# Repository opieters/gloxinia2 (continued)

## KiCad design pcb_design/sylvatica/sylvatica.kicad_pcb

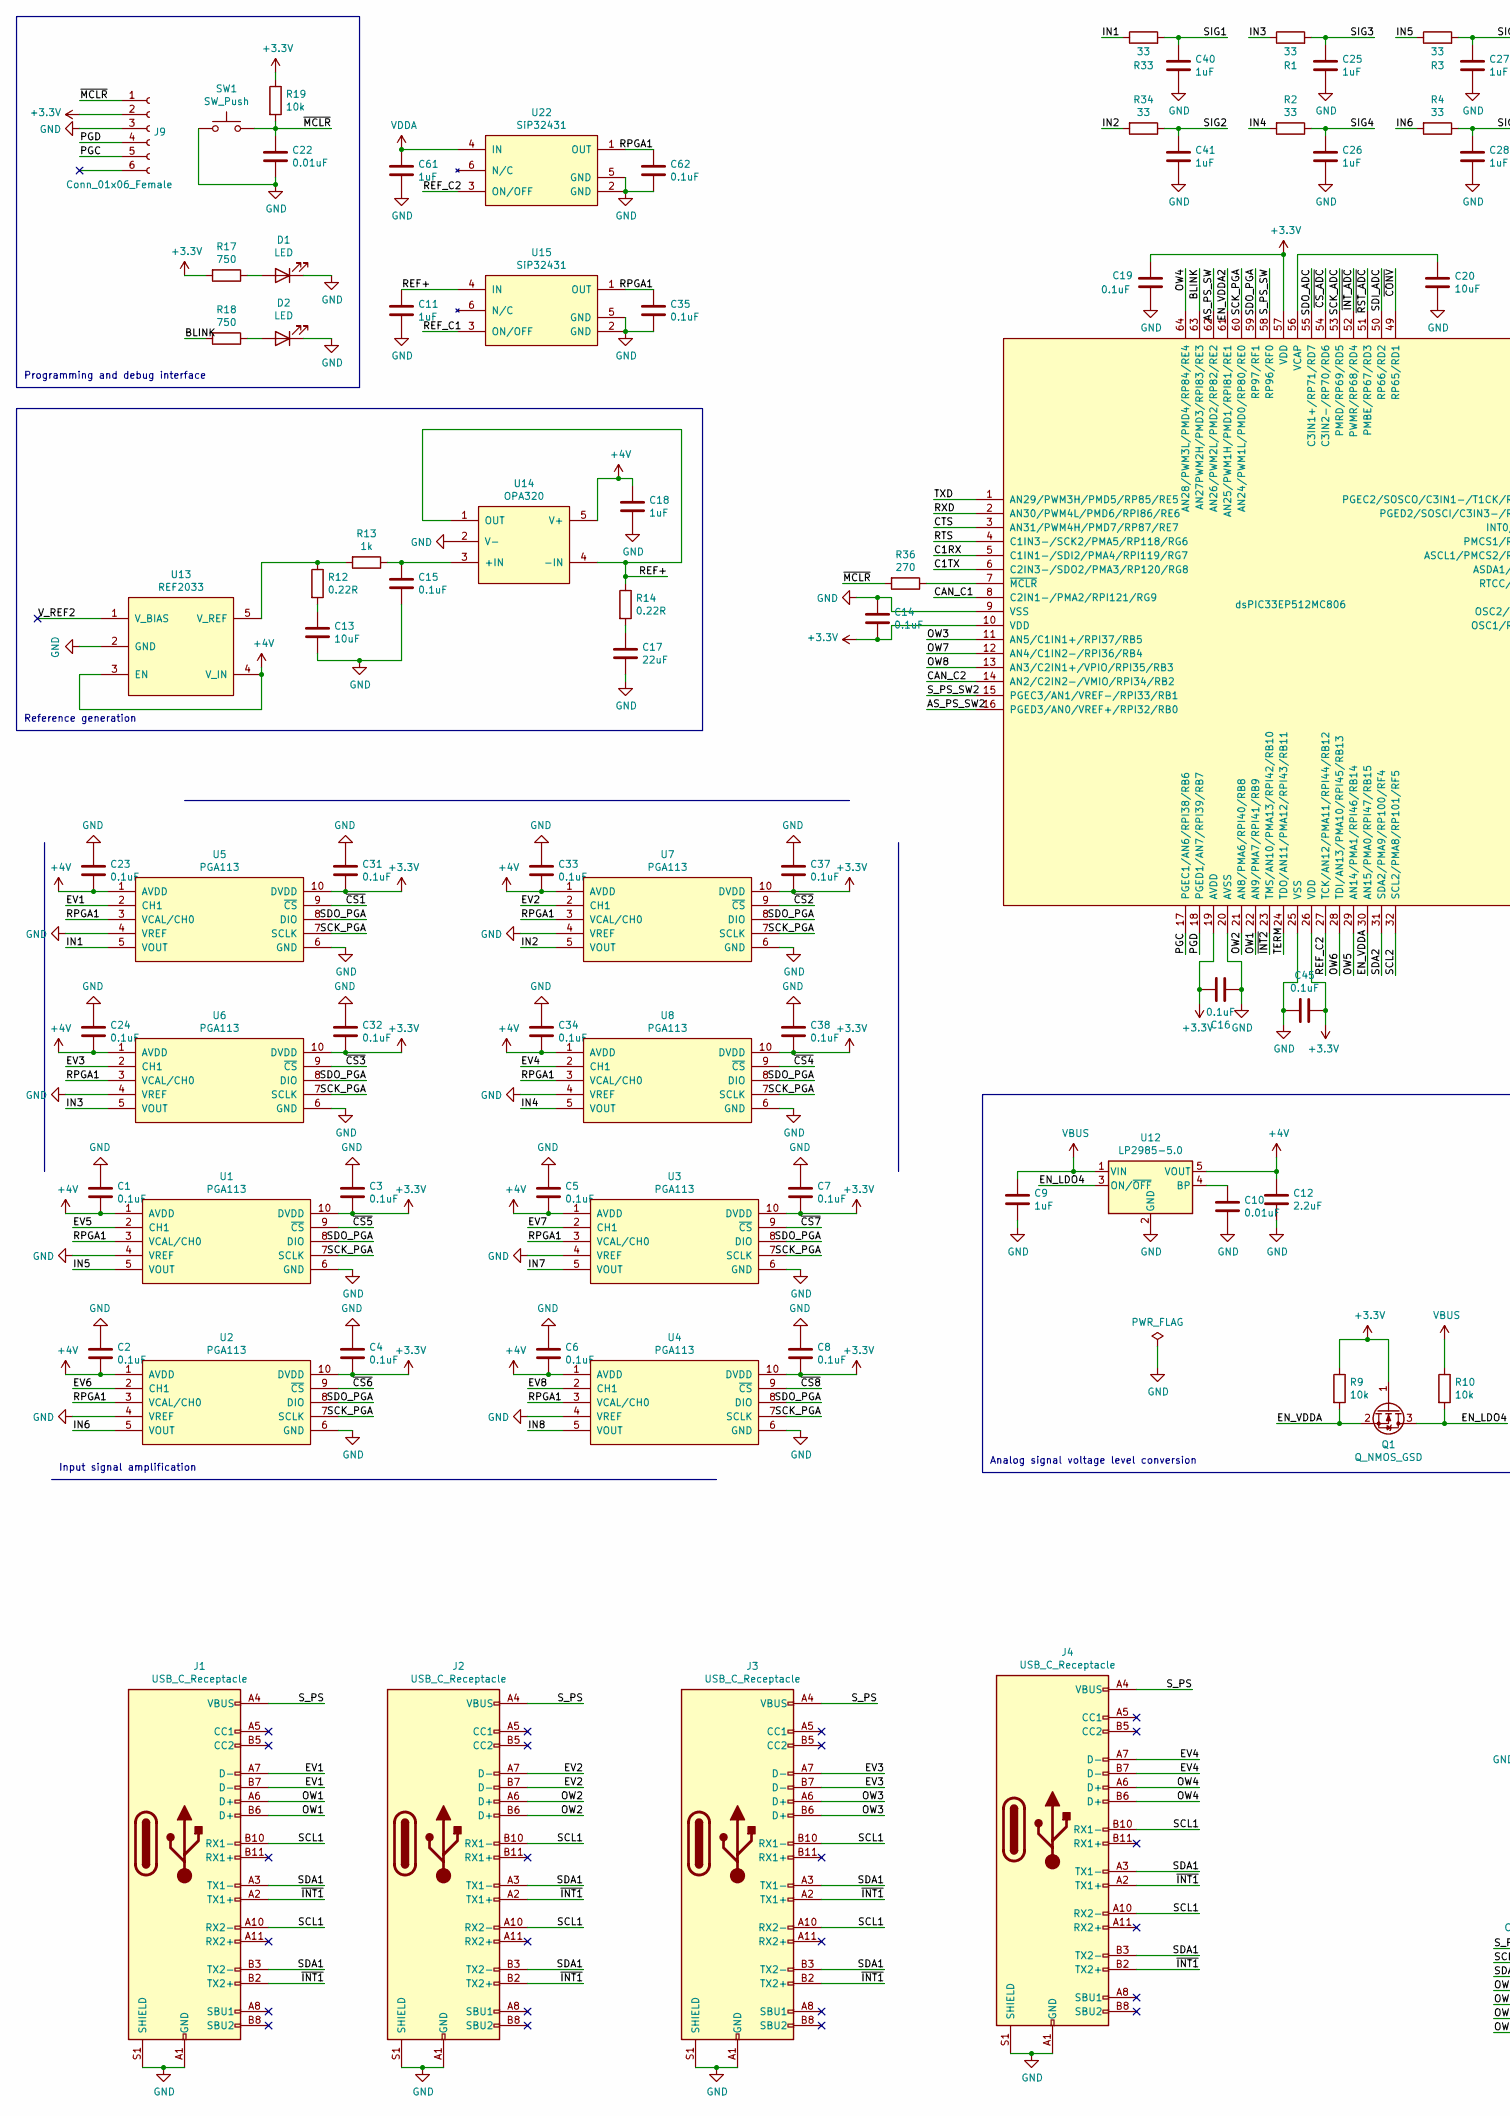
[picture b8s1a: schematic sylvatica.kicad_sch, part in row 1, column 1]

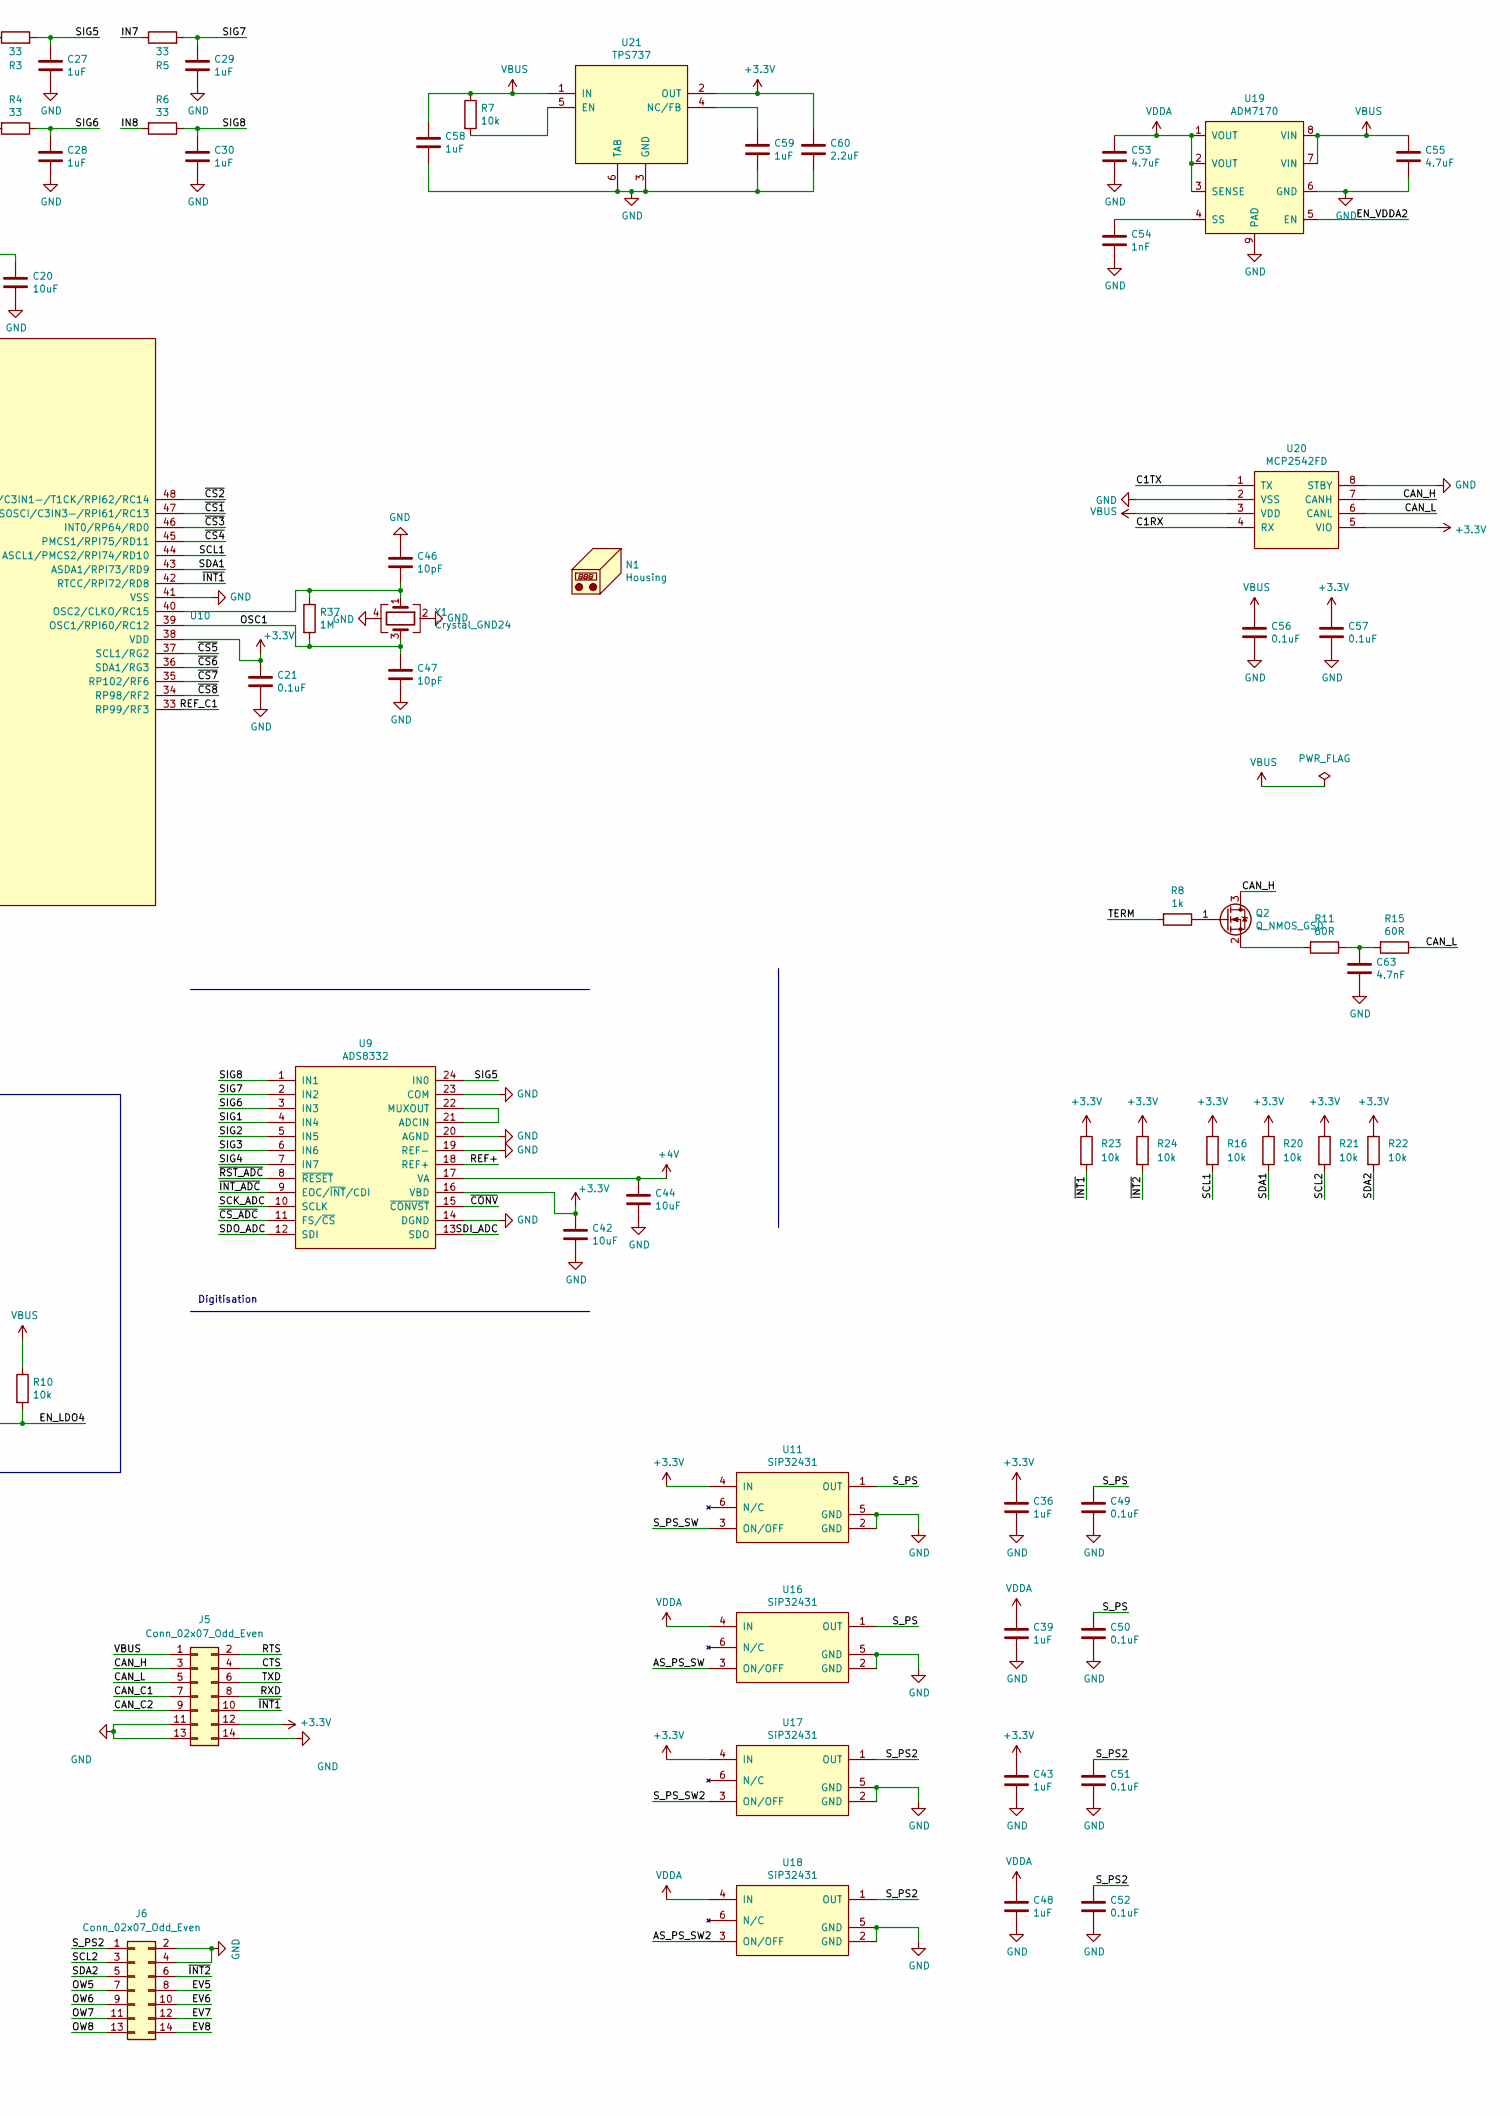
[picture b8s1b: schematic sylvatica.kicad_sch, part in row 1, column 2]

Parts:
C1, C2, C3, C4, C5, C6, C7, C8, C14, C15, C16, C19, C21, C23, C24, C31, C32, C33, C34, C35, C37, C38, C45, C62: 0.1uF; C_0603_1608Metric; Mouser 710-885012206071
C9, C11, C25, C26, C27, C28, C29, C30, C40, C41, C61: 1uF; C_0603_1608Metric; Mouser 77-VJ0603A102GXJPBC
C10, C22: 0.01uF; C_0603_1608Metric; Mouser 77-VJ0603A102GXJPBC
C12: 2.2uF; C_1206_3216Metric; Mouser 791-1206X225K250CT
C13, C20, C42, C44: 10uF; C_1210_3225Metric; Mouser 963-TMK325BJ106KM-P
C17: 22uF; C_1206_3216Metric; Mouser 963-TMK316BBJ226ML-T
C18: 1uF; C_1210_3225Metric; Mouser 963-TMK325B7105KD-T
C36, C39, C43, C48, C58, C59: 1uF; C_0603_1608Metric
C46, C47: 10pF; C_0603_1608Metric; Mouser 603-CC603FRNPO9BN100
C49, C50, C51, C52, C56, C57: 0.1uF; C_0603_1608Metric
C53, C55: 4.7uF; C_1206_3216Metric
C54: 1nF; C_0603_1608Metric
C60: 2.2uF; C_1206_3216Metric
C63: 4.7nF; C_0603_1608Metric
D1, D2: LED; LED_0603_1608Metric; Mouser 78-TLMS1000
J1, J2, J3, J4: USB_C_Receptacle; USB_C_Receptacle_Amphenol_12401861XX12A
J5, J6: Conn_02x07_Odd_Even; SAMTEC_TMMH-107-01-T-DV
J9: Conn_01x06_Female; PinSocket_1x06_P2.54mm_Vertical
N1: Housing; Enclosure-Gloxinia4
Q1: Q_NMOS_GSD; SOT-23; Mouser 512-BSS138
Q2: Q_NMOS_GSD; SOT-23; Mouser 771-PMV20XNER
R1, R2, R3, R4, R5, R6, R33, R34: 33; R_0603_1608Metric; Mouser 603-RC0603FR-0733RL
R7, R16, R20, R21, R22, R23, R24: 10k; R_0603_1608Metric
R8: 1k; R_0603_1608Metric
R9, R10, R19: 10k; R_0603_1608Metric; Mouser 284-APC0603B10K0N
R11, R15: 60R; R_0603_1608Metric; Mouser 594-5063JD120R0F
R12, R14: 0.22R; R_0603_1608Metric; Mouser 667-ERJ-3RQFR22V
R13: 1k; R_0603_1608Metric; Mouser 652-CR0603-FX1001HLF
R17, R18: 750; R_0603_1608Metric; Mouser 603-RC0603FR-07750RL
R36: 270; R_0603_1608Metric; Mouser 603-RC0603FR-07270RL
R37: 1M; R_0603_1608Metric; Mouser 603-RC0603FR-101ML
SW1: SW_Push; SW_Push_1P1T_NO_CK_KMR2; Mouser 611-KMR621NGLFS
U1, U2, U3, U4, U5, U6, U7, U8: PGA113; MSOP-10_3x3mm_P0.5mm; Mouser 595-PGA113AIDGSR
U9: ADS8332; TSSOP-24_4.4x7.8mm_P0.65mm; Mouser 595-ADS8332IBPWR
U10: dsPIC33EP512MC806; TQFP-64_10x10mm_P0.5mm; Mouser 579-33EP512MC806IPT
U11, U16, U17, U18: SiP32431; SOT-363_SC-70-6
U12: LP2985-5.0; SOT-23-5; Mouser 926-LP2985IM540NOPB
U13: REF2033; SOT-23-5; Mouser 595-REF2033AIDDCR
U14: OPA320; SOT-23-5; Mouser 595-OPA320AIDBVR
U15, U22: SiP32431; SOT-363_SC-70-6; Mouser 781-SIP32431DR3-GE3
U19: ADM7170; LFCSP-8-1EP_3x3mm_P0.5mm_EP1.45x1.74mm
U20: MCP2542FD; SOIC-8_3.9x4.9mm_P1.27mm; Mouser 579-MCP2542FDT-E/SN
U21: TPS737; SOT-223-6
Y1: Crystal_GND24; Crystal_SMD_Abracon_ABM3B-4Pin_5.0x3.2mm; Mouser 520-80-10-30B-CWNT

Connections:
+3.3V: C3.2, C4.2, C7.2, C8.2, C14.2, C16.1, C19.1, C21.1, C31.2, C32.2, C36.1, C37.2, C38.2, C42.1, C43.1, C45.1, C57.1, C60.1, J5.12, J9.2, Q1.1 (G), R9.1, R16.1, R17.2, R19.1, R20.1, R21.1, R22.1, R23.1, R24.1, U1.10 (DVDD), U2.10 (DVDD), U3.10 (DVDD), U4.10 (DVDD), U5.10 (DVDD), U6.10 (DVDD), U7.10 (DVDD), U8.10 (DVDD), U9.16 (VBD), U10.10 (VDD), U10.19 (AVDD), U10.26 (VDD), U10.38 (VDD), U10.57 (VDD), U11.4 (IN), U17.4 (IN), U20.5 (VIO), U21.2 (OUT)
+4V: C1.2, C2.2, C5.2, C6.2, C12.1, C18.1, C23.2, C24.2, C33.2, C34.2, C44.1, U1.1 (AVDD), U2.1 (AVDD), U3.1 (AVDD), U4.1 (AVDD), U5.1 (AVDD), U6.1 (AVDD), U7.1 (AVDD), U8.1 (AVDD), U9.17 (VA), U12.5 (VOUT), U13.3 (EN), U13.4 (V_IN), U14.5 (V+)
/AS_PS_SW: U10.62 (AN26/PWM2L/PMD2/RP82/RE2), U16.3 (ON/OFF)
/AS_PS_SW2: U10.16 (PGED3/AN0/VREF+/RPI32/RB0), U18.3 (ON/OFF)
/BLINK: R18.2, U10.63 (AN27PWM2H/PMD3/RPI83/RE3)
/C1RX: U10.5 (C1IN1-/SDI2/PMA4/RPI119/RG7), U20.4 (RX)
/C1TX: U10.6 (C2IN3-/SDO2/PMA3/RP120/RG8), U20.1 (TX)
/CAN_C1: J5.7, U10.8 (C2IN1-/PMA2/RPI121/RG9)
/CAN_C2: J5.9, U10.14 (AN2/C2IN2-/VMIO/RPI34/RB2)
/CAN_H: J5.3, Q2.3 (D), U20.7 (CANH)
/CAN_L: J5.5, R15.1, U20.6 (CANL)
/CTS: J5.4, U10.3 (AN31/PWM4H/PMD7/RP87/RE7)
/EN_LDO4: Q1.3 (D), R10.2, U12.3 (ON/~OFF)
/EN_VDDA: Q1.2 (S), R9.2, U10.30 (AN15/PMA0/RPI47/RB15)
/EN_VDDA2: U10.61 (AN25/PWM1H/PMD1/RPI81/RE1), U19.5 (EN)
/EV1: J1.A7 (D-), J1.B7 (D-), U5.2 (CH1)
/EV2: J2.A7 (D-), J2.B7 (D-), U7.2 (CH1)
/EV3: J3.A7 (D-), J3.B7 (D-), U6.2 (CH1)
/EV4: J4.A7 (D-), J4.B7 (D-), U8.2 (CH1)
/EV5: J6.8, U1.2 (CH1)
/EV6: J6.10, U2.2 (CH1)
/EV7: J6.12, U3.2 (CH1)
/EV8: J6.14, U4.2 (CH1)
/IN1: R33.1, U5.5 (VOUT)
/IN2: R34.2, U7.5 (VOUT)
/IN3: R1.1, U6.5 (VOUT)
/IN4: R2.2, U8.5 (VOUT)
/IN5: R3.1, U1.5 (VOUT)
/IN6: R4.2, U2.5 (VOUT)
/IN7: R5.1, U3.5 (VOUT)
/IN8: R6.2, U4.5 (VOUT)
/OSC1: C47.1, R37.2, U10.39 (OSC1/RPI60/RC12), Y1.3
/OW1: J1.A6 (D+), J1.B6 (D+), U10.22 (AN9/PMA7/RPI41/RB9)
/OW2: J2.A6 (D+), J2.B6 (D+), U10.21 (AN8/PMA6/RPI40/RB8)
/OW3: J3.A6 (D+), J3.B6 (D+), U10.11 (AN5/C1IN1+/RPI37/RB5)
/OW4: J4.A6 (D+), J4.B6 (D+), U10.64 (AN28/PWM3L/PMD4/RP84/RE4)
/OW5: J6.7, U10.29 (AN14/PMA1/RPI46/RB14)
/OW6: J6.9, U10.28 (TDI/AN13/PMA10/RPI45/RB13)
/OW7: J6.11, U10.12 (AN4/C1IN2-/RPI36/RB4)
/OW8: J6.13, U10.13 (AN3/C2IN1+/VPIO/RPI35/RB3)
/PGC: J9.5, U10.17 (PGEC1/AN6/RPI38/RB6)
/PGD: J9.4, U10.18 (PGED1/AN7/RPI39/RB7)
/REF+: C11.1, R14.1, U9.18 (REF+), U14.1 (OUT), U14.4 (-IN), U15.4 (IN)
/REF_C1: U10.33 (RP99/RF3), U15.3 (ON/OFF)
/REF_C2: U10.27 (TCK/AN12/PMA11/RPI44/RB12), U22.3 (ON/OFF)
/RPGA1: C35.1, C62.1, U1.3 (VCAL/CH0), U2.3 (VCAL/CH0), U3.3 (VCAL/CH0), U4.3 (VCAL/CH0), U5.3 (VCAL/CH0), U6.3 (VCAL/CH0), U7.3 (VCAL/CH0), U8.3 (VCAL/CH0), U15.1 (OUT), U22.1 (OUT)
/RTS: J5.2, U10.4 (C1IN3-/SCK2/PMA5/RP118/RG6)
/RXD: J5.8, U10.2 (AN30/PWM4L/PMD6/RPI86/RE6)
/SCK_ADC: U9.10 (SCLK), U10.53 (PMRD/RP69/RD5)
/SCK_PGA: U1.7 (SCLK), U2.7 (SCLK), U3.7 (SCLK), U4.7 (SCLK), U5.7 (SCLK), U6.7 (SCLK), U7.7 (SCLK), U8.7 (SCLK), U10.60 (AN24/PWM1L/PMD0/RP80/RE0)
/SCL1: J1.A10 (RX2-), J1.B10 (RX1-), J2.A10 (RX2-), J2.B10 (RX1-), J3.A10 (RX2-), J3.B10 (RX1-), J4.A10 (RX2-), J4.B10 (RX1-), R16.2, U10.44 (ASCL1/PMCS2/RPI74/RD10)
/SCL2: J6.3, R21.2, U10.32 (SCL2/PMA8/RP101/RF5)
/SDA1: J1.A3 (TX1-), J1.B3 (TX2-), J2.A3 (TX1-), J2.B3 (TX2-), J3.A3 (TX1-), J3.B3 (TX2-), J4.A3 (TX1-), J4.B3 (TX2-), R20.2, U10.43 (ASDA1/RPI73/RD9)
/SDA2: J6.5, R22.2, U10.31 (SDA2/PMA9/RP100/RF4)
/SDI_ADC: U9.13 (SDO), U10.50 (RP66/RD2)
/SDO_ADC: U9.12 (SDI), U10.55 (C3IN1+/RP71/RD7)
/SDO_PGA: U1.8 (DIO), U2.8 (DIO), U3.8 (DIO), U4.8 (DIO), U5.8 (DIO), U6.8 (DIO), U7.8 (DIO), U8.8 (DIO), U10.59 (RP97/RF1)
/SIG1: C40.1, R33.2, U9.4 (IN4)
/SIG2: C41.1, R34.1, U9.5 (IN5)
/SIG3: C25.1, R1.2, U9.6 (IN6)
/SIG4: C26.1, R2.1, U9.7 (IN7)
/SIG5: C27.1, R3.2, U9.24 (IN0)
/SIG6: C28.1, R4.1, U9.3 (IN3)
/SIG7: C29.1, R5.2, U9.2 (IN2)
/SIG8: C30.1, R6.1, U9.1 (IN1)
/S_PS: C49.1, C50.1, J1.A4 (VBUS), J1.A9 (VBUS), J1.B4 (VBUS), J1.B9 (VBUS), J2.A4 (VBUS), J2.A9 (VBUS), J2.B4 (VBUS), J2.B9 (VBUS), J3.A4 (VBUS), J3.A9 (VBUS), J3.B4 (VBUS), J3.B9 (VBUS), J4.A4 (VBUS), J4.A9 (VBUS), J4.B4 (VBUS), J4.B9 (VBUS), U11.1 (OUT), U16.1 (OUT)
/S_PS2: C51.1, C52.1, J6.1, U17.1 (OUT), U18.1 (OUT)
/S_PS_SW: U10.58 (RP96/RF0), U11.3 (ON/OFF)
/S_PS_SW2: U10.15 (PGEC3/AN1/VREF-/RPI33/RB1), U17.3 (ON/OFF)
/TERM: R8.2, U10.24 (TDO/AN11/PMA12/RPI43/RB11)
/TXD: J5.6, U10.1 (AN29/PWM3H/PMD5/RP85/RE5)
/V_REF2: U13.1 (V_BIAS)
/~CONV: U9.15 (~CONVST), U10.49 (RP65/RD1)
/~CS1: U5.9 (~CS), U10.47 (PGED2/SOSCI/C3IN3-/RPI61/RC13)
/~CS2: U7.9 (~CS), U10.48 (PGEC2/SOSCO/C3IN1-/T1CK/RPI62/RC14)
/~CS3: U6.9 (~CS), U10.46 (INT0/RP64/RD0)
/~CS4: U8.9 (~CS), U10.45 (PMCS1/RPI75/RD11)
/~CS5: U1.9 (~CS), U10.37 (SCL1/RG2)
/~CS6: U2.9 (~CS), U10.36 (SDA1/RG3)
/~CS7: U3.9 (~CS), U10.35 (RP102/RF6)
/~CS8: U4.9 (~CS), U10.34 (RP98/RF2)
/~CS_ADC: U9.11 (FS/~CS), U10.54 (C3IN2-/RP70/RD6)
/~INT1: J1.A2 (TX1+), J1.B2 (TX2+), J2.A2 (TX1+), J2.B2 (TX2+), J3.A2 (TX1+), J3.B2 (TX2+), J4.A2 (TX1+), J4.B2 (TX2+), J5.10, R23.2, U10.42 (RTCC/RPI72/RD8)
/~INT2: J6.6, R24.2, U10.23 (TMS/AN10/PMA13/RPI42/RB10)
/~INT_ADC: U9.9 (EOC/~INT/CDI), U10.52 (PWMR/RP68/RD4)
/~MCLR: C22.1, J9.1, R19.2, R36.2, SW1.2
/~RST_ADC: U9.8 (~RESET), U10.51 (PMBE/RP67/RD3)
GND: C1.1, C2.1, C3.1, C4.1, C5.1, C6.1, C7.1, C8.1, C9.2, C10.2, C11.2, C12.2, C13.2, C14.1, C15.2, C16.2, C17.2, C18.2, C19.2, C20.2, C21.2, C22.2, C23.1, C24.1, C25.2, C26.2, C27.2, C28.2, C29.2, C30.2, C31.1, C32.1, C33.1, C34.1, C35.2, C36.2, C37.1, C38.1, C39.2, C40.2, C41.2, C42.2, C43.2, C44.2, C45.2, C46.1, C47.2, C48.2, C49.2, C50.2, C51.2, C52.2, C53.2, C54.2, C55.2, C56.2, C57.2, C58.2, C59.2, C60.2, C61.2, C62.2, C63.2, D1.1 (K), D2.1 (K), J1.A1 (GND), J1.A12 (GND), J1.B1 (GND), J1.B12 (GND), J1.S1 (SHIELD), J2.A1 (GND), J2.A12 (GND), J2.B1 (GND), J2.B12 (GND), J2.S1 (SHIELD), J3.A1 (GND), J3.A12 (GND), J3.B1 (GND), J3.B12 (GND), J3.S1 (SHIELD), J4.A1 (GND), J4.A12 (GND), J4.B1 (GND), J4.B12 (GND), J4.S1 (SHIELD), J5.11, J5.13, J5.14, J6.2, J6.4, J9.3, SW1.1, U1.4 (VREF), U1.6 (GND), U2.4 (VREF), U2.6 (GND), U3.4 (VREF), U3.6 (GND), U4.4 (VREF), U4.6 (GND), U5.4 (VREF), U5.6 (GND), U6.4 (VREF), U6.6 (GND), U7.4 (VREF), U7.6 (GND), U8.4 (VREF), U8.6 (GND), U9.14 (DGND), U9.19 (REF-), U9.20 (AGND), U9.23 (COM), U10.9 (VSS), U10.20 (AVSS), U10.25 (VSS), U10.41 (VSS), U11.2 (GND), U11.5 (GND), U12.2 (GND), U13.2 (GND), U14.2 (V-), U15.2 (GND), U15.5 (GND), U16.2 (GND), U16.5 (GND), U17.2 (GND), U17.5 (GND), U18.2 (GND), U18.5 (GND), U19.6 (GND), U19.9 (PAD), U20.2 (VSS), U20.8 (STBY), U21.3 (GND), U21.6 (TAB), U22.2 (GND), U22.5 (GND), Y1.2, Y1.4
unnamed: C10.1, U12.4 (BP)
unnamed: C13.1, R12.2
unnamed: C15.1, R13.1, U14.3 (+IN)
unnamed: C17.1, R14.2
unnamed: C20.1, U10.56 (VCAP)
unnamed: C46.2, R37.1, U10.40 (OSC2/CLKO/RC15), Y1.1
unnamed: C54.1, U19.4 (SS)
unnamed: C59.1, U21.4 (NC/FB)
unnamed: C63.1, R11.1, R15.2
unnamed: D1.2 (A), R17.1
unnamed: D2.2 (A), R18.1
unnamed: Q2.1 (G), R8.1
unnamed: Q2.2 (S), R11.2
unnamed: R7.2, U21.5 (EN)
unnamed: R12.1, R13.2, U13.5 (V_REF)
unnamed: R36.1, U10.7 (~MCLR)
unnamed: U9.21 (ADCIN), U9.22 (MUXOUT)
VBUS: C9.1, C55.1, C56.1, C58.1, J5.1, R7.1, R10.1, U12.1 (VIN), U19.7 (VIN), U19.8 (VIN), U20.3 (VDD), U21.1 (IN)
VDDA: C39.1, C48.1, C53.1, C61.1, U16.4 (IN), U18.4 (IN), U19.1 (VOUT), U19.2 (VOUT), U19.3 (SENSE), U22.4 (IN)

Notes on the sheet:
Reference generation
Digitisation
Input signal amplification
Analog signal voltage level conversion
Programming and debug interface

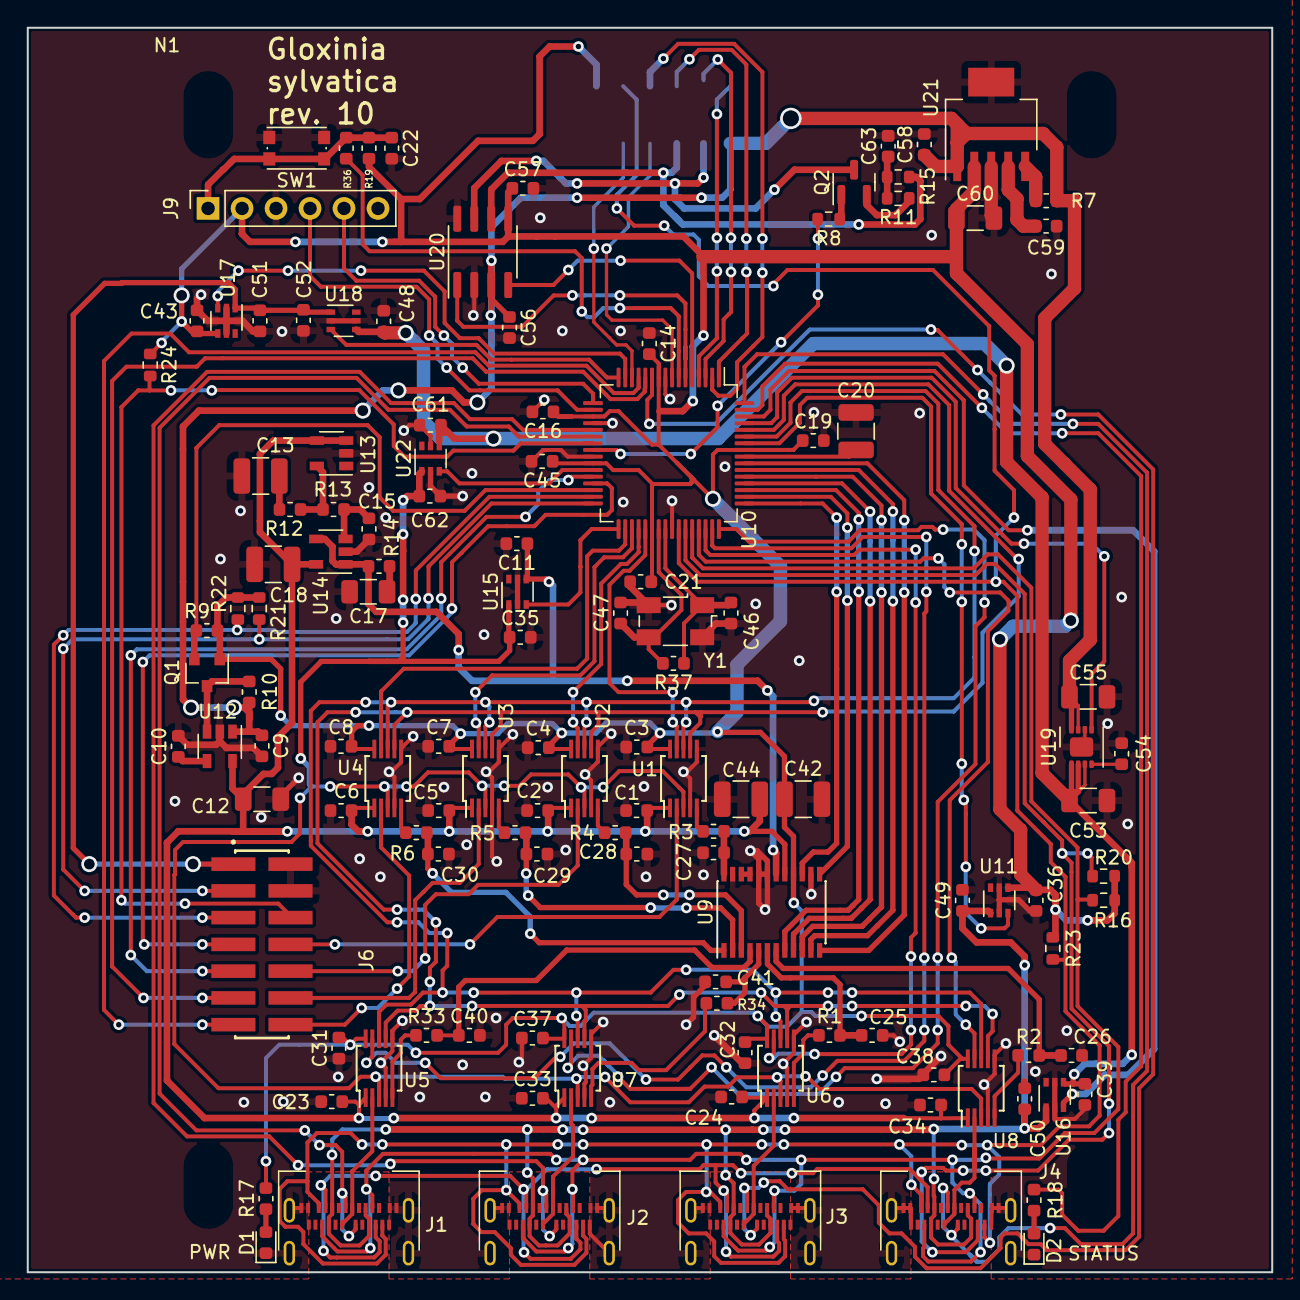
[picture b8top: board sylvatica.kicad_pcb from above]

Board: 2 copper layers, 93.0 x 93.0 mm, 127 parts (1 on the bottom side), 106 nets.

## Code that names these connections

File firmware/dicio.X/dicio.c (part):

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    switch(vconfig)
    {
        case INTERFACE_SUPPY_ANALOGUE:
            _RB5 = 0;
            __delay_us(10);
            _RB8 = 1;
            break;
        case INTERFACE_SUPPLY_DIGITAL:
            _RB8 = 0;
            __delay_us(10);
            _RB5 = 1;
            break;
        default:
            return;
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     */

    _ANSE5 = 0;
    _TRISE5 = 0; // U1 RTS
    _RP85R = _RPOUT_U1RTS;

    _ANSG6 = 0;
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    _RP118R = _RPOUT_U1TX;

    _ANSG7 = 0;
    _TRISG7 = 1; // U1 CTS
    _U1CTSR = 119;

    _ANSG8 = 0;
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    _ANSB10 = 0; // CAN C2
    _TRISB10 = 1;
    _CNPDB10 = 1; // enable pull-down
    _ANSB14 = 0;  // TERM
    _TRISB14 = 0;
    _LATB14 = 0;
    _ANSB9 = 0; // SYNC
    _TRISB9 = 1;

    /*
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     */
    _TRISD6 = 1; // SDI1
    _SDI1R = 70;
    _TRISD1 = 0; // SCK1
    _RP65R = _RPOUT_SCK1;
    _TRISD0 = 0; // SDO1
    _RP64R = _RPOUT_SDO1;
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    _ANSE0 = 0; // SI
    _TRISE0 = 0;
    _SDI3R = 80;
    _TRISD7 = 0; // SQICLK
    _RP71R = _RPOUT_SCK3;
    _ANSG6 = 0;
    _TRISF1 = 0; // SO
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
    _ANSB4 = 0;  // configure nINT1 as digital pin
    _TRISB4 = 1; // configure nINT1 as digital output pin
    _RB4 = 0;
    //_CNPUB4 = 1;

    /*
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
    _ANSE2 = 0;  // configure nINT2 as digital pin
    _TRISE2 = 1; // configure nINT2 as digital input pin
    //_RE2 = 1;
    //_CNPUE2 = 1;

    /*
     * communication UART
     */
    _TRISF6 = 0; // U2 RTS
    _RP102R = _RPOUT_U2RTS;
    _ANSB12 = 0; // U2 CTS
    _U2CTSR = 44;
    _TRISB12 = 1;
    _TRISF2 = 1; // U2 RX
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    /*
     * debug UART
     */
    _ANSE5 = 0; // U1 RTS
    _TRISE5 = 0;
    _RP85R = _RPOUT_U1RTS;
    _ANSG7 = 0; // U1 CTS
    _U1CTSR = 119;
    _TRISG7 = 1;
    _ANSG6 = 0; // U1 TX
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    _ANSB13 = 0; // CAN1 RX
    _TRISB13 = 1;
    _C1RXR = 45;
    _ANSB14 = 0; // TERM 
    _TRISB14 = 0;
    _LATB14 = 1;
    _ANSB11 = 0; // CAN_C1
    _TRISB11 = 1;
    _ANSB10 = 0; // CAN_C2
    _TRISB10 = 1;
    
    /* 
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     */
    _ANSD6 = 0;
    _TRISD6 = 1;// SDI
     _RD6 = 0;
    //_SDI3R = 70; 
    //_ANSD5 = 0;
    _TRISD5 = 1;
    _RD5 = 0;
    _SDI1R = 70;
    
    _TRISD1 = 0; // SCK
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    _RP64R = _RPOUT_SDO1;
    
    _TRISD11 = 0;  // CS
    _RD11 = 1;
    
    /*
     * SPI configuration
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    _LATD4 = 1;
    _TRISF1 = 0; // SO
    _RP97R = _RPOUT_SDO3;
    _ANSD7 = 0; // SQICLK
    _TRISD7 = 0;
    _RP71R = _RPOUT_SCK3;
    _ANSE0 = 0; // SI
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    /*
     * misc configuration
     */
    _ANSB9 = 0; // SYNC
    _TRISB9 = 1; 
    _LATD9 = 0;
    _TRISD8 = 1; // BTN
    _LATD8 = 0;
    _ANSB8 = 0;// EN_VA
    _TRISB8 = 0; 
    _LATB8 = 0;
    _ANSB5 = 0; // S_PS_SW
    _TRISB5 = 0;
    _LATB5 = 0;
    _TRISG3 = 0; // ERR (LED)
    _LATG3 = 0;

    
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}

void __attribute__((interrupt, no_auto_psv)) _CNInterrupt(void) {
    if((_RE6 == 0) && (pin_interrupt_tasks[0].cb != NULL))
    {
        push_queued_task(&pin_interrupt_tasks[0]);
    }
    if((_RE7 == 0) && (pin_interrupt_tasks[1].cb != NULL))
    {
        push_queued_task(&pin_interrupt_tasks[1]);
    }
    if((_RB3 == 0) && (pin_interrupt_tasks[2].cb != NULL))
    {
        push_queued_task(&pin_interrupt_tasks[2]);
    }
    if((_RB1 == 0) && (pin_interrupt_tasks[3].cb != NULL))
    {
        push_queued_task(&pin_interrupt_tasks[3]);
    }
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
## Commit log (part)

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2022-02-28 Add ignore file.
2022-02-28 Started redesign of dicio for Gloxinia2
2022-04-15 Enclosure design.
2022-04-15 Generate BOM
2022-04-15 Components
2022-04-15 More components
2022-04-15 New dicio design.
2022-04-15 Dicio design with PIC32 MCU
2022-04-15 New planalta design.
2022-04-15 Side connector PCB
2022-04-15 Update.
2022-04-21 Updated enclosure based on first design run.
2022-04-21 Redesign for improved mounting hole placement.
2022-04-21 Partial redesign.
2022-09-01 Firmware
2022-09-01 Basic GUI for demonstrations
2022-09-01 New design
2022-09-01 New components
2022-09-20 Move folder
2022-09-20 Initial version of Qt GUI
2022-09-29 New version.
2022-10-13 Various improvements to the enclusure design.
2022-10-13 Start reworking software to more suitable design.
2022-10-13 Placement update.
2022-10-26 Remove old project
2022-10-26 Clean project
2022-11-03 Implemented node discovery
2022-11-03 Functional node discovery
2022-11-03 Rename files and remove old one
2022-11-15 Overall readbility improved and CAN bug fix.
2022-11-15 Remove PIC32 project.
2022-11-15 Remove old project file.
2022-11-21 First version with functional address acquisition
2022-11-23 Various improvements and bug fixes :D
2022-11-24 SHT35 sensor can now be partially configured
2022-12-05 Start working on sylvatica software.
2022-12-05 Main sylvatica file.
2022-12-05 Add sensor config readout option.
2022-12-05 Various improvements.
2022-12-05 Ignore some directories in new sylvatica project.
2022-12-05 Add convinience cast function from QVariant to GCNode*
2022-12-05 Add convenience cast function from QVariant to GCSensor*
2022-12-05 Added start and stop calls + status field updates now
2022-12-05 Simple node/sensor getter without using QModelIndex
2022-12-05 Updated interface with start/stop buttons
2022-12-05 Sensor status updates are now handled correctly
2022-12-05 Discard requests (cannot be issued by nodes)
2022-12-05 Remove i2c bus field for SHT35
2022-12-05 Simplify readout handling.
2022-12-05 UART communication is now reliable
    - Enabled hardware flow control to prevent messages from disapearing.
    - Removed delays.
    - Added more powerful RX system in gloxinia where messages are
    processed in the main loop instead of during the interrupt.
2022-12-06 Bug fix: interrupts were not re-enabled.
    When running `schedule_remove_event`, it was possible that
    interrupts were not re-enabled if the id was not found.
2022-12-06 Bug fix: status message handling.
    Status message updates from the gateway were not handled correctly,
    resulting in no updates in most cases.
2022-12-06 Improved error/status logging and bug fixes.
    Fixed several status updates which were initialised, but not transmitted.
    Overall improvements to initialisation and error reporting.
2022-12-06 Added error report enum.
2022-12-06 Improved error reporting functionalities.
2022-12-06 Handle sensor data correctly.
2022-12-06 Various improvements and updates.
2022-12-06 Add proper implementation of destructor.
    `file` resulted in a memory leak before.
2023-01-06 These documents should contain the documentation of the different connectors and hardware usage.
2023-01-06 Bug fix: id was not assigned. Added error logging.
2023-01-06 Add new files for additional functionality.
2023-01-06 Add code
2023-01-06 Set application parameters.
2023-01-06 New and updated board designs.
2023-01-09 Add error message when project settings not valid.
2023-01-09 More logical code
2023-01-09 Improve file open/save
2023-01-09 Bug fix: path creation and file opening
2023-01-09 Bug fixes
    Start measuring did not create a unique directory
    Sensor removal memory leak fixed
    Sensor removal puts empty data and does not remove interface
    Add sensor removed from context menu
2023-01-12 Bug fixes
2023-01-12 Add stop sensor command.
2023-01-12 Bug fixes and readout improvements to prevent errors from triggering
2023-01-12 Add get status method and bug fixes
2023-01-12 Set default value to period.
2023-01-12 Simplifcation of code.
2023-01-13 Implement application settings dialog
2023-01-13 Limit number of messages displayed
2023-01-13 Add sensor plot functionality
2023-01-16 Updated APDS9306 065 integration
2023-01-17 Also save some application settings, merge two structs on application/project settings
2023-01-17 Bug fixes.
    Settings defined in preferences are now correctly served. Data duplication removed.
    Add plot and delete options are now disabled for empty sensor interfaces
2023-01-17 Optimisation to make sensor starts more logical
2023-01-17 Add global measurement period to saved data
2023-01-17 Simplify sensor editing
2023-01-17 Check if data is empty
2023-01-17 Add new processor for sensor config
2023-01-18 Use updated structure to send messages in the entire project
2023-01-19 Expose RTCC pin for synchronisation
2023-01-19 Set default pointer values
2023-01-19 Update start/stop bytes
2023-01-19 Make widgets resizable
2023-01-19 Rework
2023-01-19 Bug fixes for APDS9306
    Plot was not added
    File check when writing to unopened sensor (state mismatch)
2023-01-19 Add elements
2023-01-19 Start adding RTCC implementation
2023-01-19 Impoved message handling and error reporting
2023-01-19 Bug fix: old behaviour removed for newer start5/stop
2023-01-19 Bug fixes, works stable now
2023-01-19 New definitions added
2023-01-23 Bug fix in component layout
    Connector was not updated to latest version, resulting in mis alignment w.r.t. connector board.
2023-01-31 Change some component sizes
2023-01-31 Improved processing.
2023-02-02 Removed depricated project
2023-02-02 Add UART bootloader
2023-02-02 Add bootloader integration
2023-02-09 Renamed file
2023-02-09 Prepare for bootloader integration.
2023-02-09 UART bootloader
2023-02-09 First attempt to integrate bootloader
2023-02-09 Add bootloader dialog.
2023-02-16 Working bootloader
2023-02-16 CAN bootloader
2023-02-16 Remove debug project and merge back into main project
2023-02-16 Add documentation
2023-02-22 Added documentation.
2023-02-22 Formatting.
2023-02-23 Added remaining documentation.
2023-02-23 Base sylvatica project
2023-02-24 Added CAN functionality to bootloader.
    The documentation is incomplete.
2023-02-24 Continue working on sylvatica project.
2023-03-01 Some reformatting
2023-03-01 Start work on use of interal 12-bit ADC
2023-03-01 Refactor UART bootloader
2023-03-06 Add missing header
2023-03-06 Add message handling for M_SENSOR_CONFIG_END
2023-03-06 Add support for internal ADC
2023-03-06 comment unused methods
2023-04-06 Rename file.
2023-04-06 Bug fix: file renamed
2023-04-06 Addnew planalta project
2023-04-06 Bug fix: renamed file.
2023-04-06 Files.
2023-04-17 Fix issue with labeling.
2023-04-17 SPI bug fixes.
2023-04-17 Update for new hardware.
2023-04-17 Ignore dev folders
2023-04-25 Working version of planalta
2023-05-05 Refactored code for more performant sensor config and added first versions of LIA en ADC16 sensors.
2023-05-09 Flip X/Y memory requirement
2023-05-09 Update code.
2023-05-09 Finish rerouting VBUS/5V net
2023-05-17 Add filtering structure for ADC12.
2023-05-23 Move Fuse config to old location
2023-05-23 Add sensor interfaces
2023-05-23 Auto configure CAN interface to accept messages with configured address.
2023-05-24 Refactoring.
2023-05-24 Functional CAN bus communication
2023-05-24 Bug fixes and increased UART logging.
2023-05-24 Reduce memory footprint.
2023-05-24 Various regressions and performance improvements.
2023-05-24 Reduced number of filter taps.
2023-05-24 Diable timer (for now)
2023-06-07 Add code to move data to right interface.
2023-06-07 Definitions of dicio ADC12 filtering.
2023-06-07 Improve address allocation search based on node type.
2023-06-07 Fix data size of messages.
2023-06-07 Correct implementation with eds address.
2023-06-07 Variuos improvements and stabilisations.
2023-06-07 Improved GUI
2023-06-08 Use separate interface ID in place of old merged system
2023-06-08 Bug fix: show ADC12 menu in place of APDS9306 menu
2023-06-08 Add ADC12 files.
2023-06-08 Bug fixes and code quality improvements.
2023-06-08 Bug fixes to follow new interface.
2023-06-09 Change addressing order
2023-06-13 Bug fix: ADC12 was used in place of ADC16
2023-06-13 Add ADC16 support and start refactoring message queue.
2023-06-13 Fix EDS-related issues.
2023-06-16 Simplify code.
2023-06-16 Fix incorrect interface bug.
2023-06-16 Bug fix
    Incorrect pointer was retunred in GCNode::fromQVariant.
2023-06-16 Remove depricated analogue config code.
2023-06-16 Fix timer/threading bug.
2023-06-16 Add LIA, remove depricated code.
2023-06-16 LIA dialogue.
2023-06-16 Add auto gain setting.
2023-06-16 Add auto gain config to GUI
2023-06-16 Remove old file.
2023-06-16 Improve toString consistency of GCSensor
2023-06-16 Update to new pin configuration.
2023-06-16 Add interfaces config and init clock
2023-06-20 Start working on SD storage
2023-06-20 Use non-bootloader DMA channel.
2023-06-20 Bug fixes and improvements.
2023-06-20 Fix incorrect app/bootloader assignment.
2023-06-27 Add first version of SD storage functionality
2023-06-27 Add support for LIA
2023-06-27 Move ADC16 hardware config outside of 16-bit analog sensor definition
2023-08-02 Remove old library code.
2023-08-02 Fix missing const.
2023-08-02 Implement data storage readout.
2023-08-02 Bug fixes.
2023-08-02 Bug fixes in SD storage implementation
2023-08-02 Reformat to follow project code conventions.
2023-08-02 Add hardware configuration.
2023-08-02 Add const to array.
2023-08-02 Remove old files.
2023-08-02 Various updates for Aisler order.
2023-08-02 New board for USB to header connector conversion.
2023-08-02 Optimisations.
2023-08-03 Rework code for message handling
2023-08-03 Rework code for message handling.
    Dicio now only uses special (dedicated) function and no longer relies on shared message_process to make code easier to maintain.
2023-08-03 Fix possible race condition when log is sent from interrupt.
2023-08-03 Remove hardware specific code.
2023-08-03 Fix sd card readout (correct timing and sequence)
2023-08-03 Remove debug file.
2023-08-03 GUI updates and opimisations.
2023-08-04 Add missing file.
2023-08-04 Improve task handling and initialisation
2023-08-04 Fix potential race condition.
2023-08-04 Add prototypes for new message types + rename other message
2023-08-04 Implement config load/store for nodes
2023-08-04 Remove duplicate definition.
2023-08-04 Disable debug prints.
2023-08-04 Add new task handling code.
2023-08-08 Only set address in one location
    This should prevent inconsistencies.
2023-08-08 If alignment.
2023-08-24 Small improvents (const) and addded docs.
2023-08-24 Various performant improvements.
2023-08-24 Documen data_write command.
2023-08-24 Improvements.
2023-08-24 Add documentation.
2023-09-05 Update for new task API.
2023-09-05 Fix some pointer issues
2023-09-05 Implement auto UART detect feature.
    A weak pull-down is used to probe for a connected UART readout.
2023-09-05 Added fn: clear delay buffers
2023-09-05 Relax processing requirement from gateway.
    Originally, only request messages were processed. Now, all are processed such that
    timing messages are also correctly handeled.
2023-09-05 Increase SPI speed and add docs on configured options.
2023-09-05 Correctly handle DAC initialisation.
2023-09-05 Improve documentation.
2023-09-05 Implement basic version of validation function.
2023-09-05 Correct error in docs.
2023-09-05 Remove todo's
2023-09-05 Improve documentation
2023-09-05 Remove depricated code.
2023-09-05 Correctly implement thread separation for serial
    The serial communcation is now properly separated into a new object and threading now works as expected.
    Some optimasation remains possible.
2023-09-05 Ownership?
2023-09-07 Merged CAn and UART bootloaders. New UART messaging format.
2023-09-21 Activate ADC12 implementation.
2023-09-21 Update messaging structure
2023-09-21 Fix error in documentation.
2023-09-21 Remove unused files.
2023-09-21 Add new components.
2023-09-21 Add new boards
2023-09-21 Update ignore file.
2023-09-25 Add new sensor: ADS1219.
2023-09-25 Correct implementation.
2023-09-25 Correctly intialise reference to ADC object
2023-10-08 Bug fixes in ADS1219 sensor implementation.
2023-10-08 Add debug code to test ADS1219
2023-10-08 Add ADS1219 sensor implementation.
2023-10-15 Major bug fixes
    GIE status was incorrectly restored
    Out of bound write in task_list fixed.
2023-10-15 Minor consistency fix
2023-10-15 Updates and bug fixes.
2023-10-17 Update for newer project structure
2023-10-19 Fix length of config message
2023-10-20 REnamed planalta project
